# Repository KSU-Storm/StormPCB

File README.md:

# StormPCB
A pcb for the K-State storm team's robot

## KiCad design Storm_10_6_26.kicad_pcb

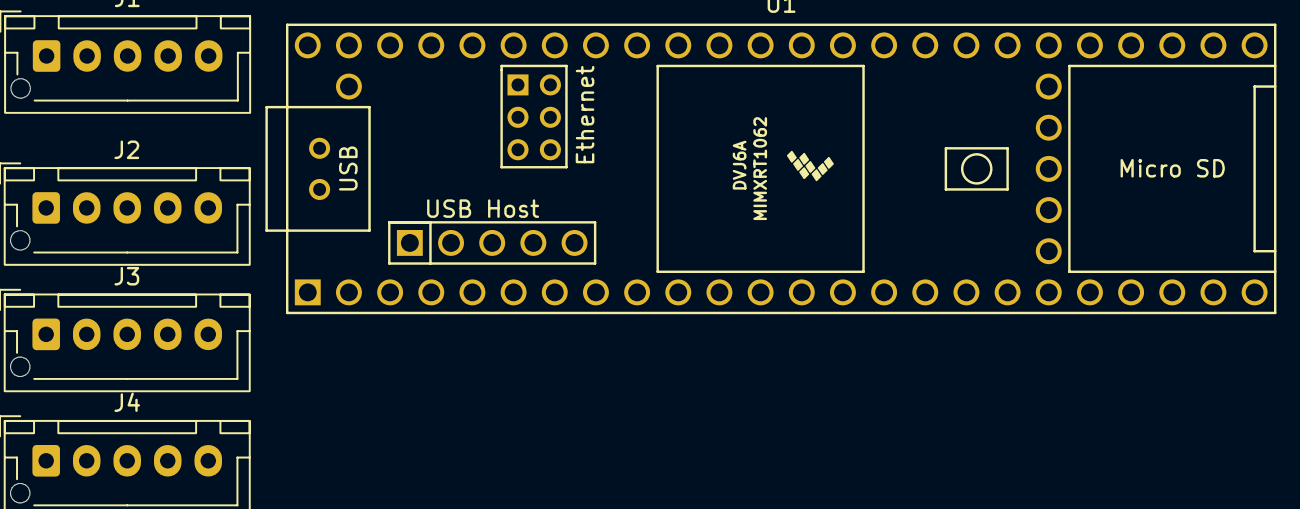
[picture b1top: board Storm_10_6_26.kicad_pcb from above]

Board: 2 copper layers, 5 parts (0 on the bottom side), 17 nets, no tracks yet.

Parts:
J1, J2, J3, J4: Conn_01x05_Pin; JST_XH_B5B-XH-AM_1x05_P2.50mm_Vertical
U1: Teensy4.1; Teensy41

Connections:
unnamed: J1.1, U1.26 (34_RX8)
unnamed: J1.2, U1.2 (0_RX1_CRX2_CS1)
unnamed: J1.3, U1.27 (35_TX8)
unnamed: J1.4, U1.3 (1_TX1_CTX2_MISO1)
unnamed: J1.5, J2.5, J3.5, J4.5, U1.47 (GND)
unnamed: J2.1, U1.28 (36_CS)
unnamed: J2.2, U1.4 (2_OUT2)
unnamed: J2.3, U1.29 (37_CS)
unnamed: J2.4, U1.5 (3_LRCLK2)
unnamed: J3.1, U1.30 (38_CS1_IN1)
unnamed: J3.2, U1.6 (4_BCLK2)
unnamed: J3.3, U1.31 (39_MISO1_OUT1A)
unnamed: J3.4, U1.9 (7_RX2_OUT1A)
unnamed: J4.1, U1.32 (40_A16)
unnamed: J4.2, U1.36 (14_A0_TX3_SPDIF_OUT)
unnamed: J4.3, U1.33 (41_A17)
unnamed: J4.4, U1.37 (15_A1_RX3_SPDIF_IN)
